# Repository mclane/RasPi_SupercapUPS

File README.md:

# RasPi_SupercapUPS
Expansion board with UPS using supercaps and a special wadchdog/undervoltage detection

## Motivation
I am running a Raspberry Pi in a holiday home. This device also  controls the heating of the water pipes in winter, so it is "mission critical". It also allows to remotly switch on the room heating via sms text messages. Regular status messages are also provided via sms. These functions have been implemented using the smart-home suite iobroker (https://www.iobroker.net/).
Since the electricity grid is sometimes unreliable, a power buffer is needed to have enough time to shut down everything in case of a power loss. Since I do not want to use the usual lithium ion battery based UPS available on the market; I was looking for an alternative and found this: https://www.hackerspace-ffm.de/wiki/index.php?title=Raspi_EDLC_UPS.
The supercaps provide enough energy to supply the raspi for 20 - 30 s which is enough for a safe shutdown. The status of the power supply is provided to one of the GPIO pins of the raspi. The status of this pin is monitored by an iobroker function and a system shutdown command is initiated if a power loss is detected.

## Requirements
- provide enough energy for a safe shutdown of the raspberry pi
- provide a power loss signal
- provide an undervoltage / power good signal to trigger a reboot after power loss
- provide a watchdog to avoid a system hangup (e.g. in case of a short power loss when undervoltage conditions are not yet met)
## Optional requirements
- provide a relay output to control room heating
- measure the actual raspberry pi supply voltage provided by the supercaps
- provide a socket for an I2C real-time clock module
## Implementation
The device is implemented as an accessory pcb to be mounted on top of the raspberry. It consists of the energy storage block and a watchdog block. Furthermore, I have added a relay to be able to switch on the electrical room heating from remote via a sms text message.
### Energy Buffer
The energy buffer consists of 2x 50F supercaps in series with a charge balancer circuit and a charge current limiting resistor. The capacitor bank is decoupled with Schottky diodes from the external power supply. Therefore, the power supply needs to provide a slightly higher voltage, e.g. 5.5V in order to obtain a 5 V supply voltage at the raspi.
### Watchdog and undervoltage detection
The boot process of the RasPi from initial startup until all ioBroker modules and functions are up and running takes about 1:20 min. This means that the watchdog timeout needs to be longer than this in order to allow a correct boot process of the system since one ioBroker function then periodically resets the watchdog timer via the GPIO22 pin. Since I could not find a watchdog IC combining a (programmable) watchdog dead time of 2 min (to be on the safe side) with a precise enough undervoltage detector, I have implemented this function using an Atmel ATTINY85 microcontroller. If an undervoltage event occurs or the watchdog timer expires, a Reset signal is applied to the RUN pin of the raspi. Even though this controller has enough memory so that the functionality could be implemented using the Arduino programming environment, I decided that I wanted to learn something new - so the functionality has been implemented in Assembler.
Since the Raspi provides an SPI interface, the ATTINY can be directly programmed using avrdude.
### Relay stage
This is straightforward: a Darlington (overdimensioned, but this was the one I had in my stock) connected to GPIO27 controls the relay. 
### Miscellaneous
Connector blocks are provided to hook up an external indicator LED for the relay and a voltmeter module to measure the raspberry pi supply voltage. Furthermore, a real-time clock module can be connected via a 4 pin header in vertical position.
## Hardware
KiCad schematics and pcb layout is provided in the hardware directory; Gerber and drill files can be found in the CAM subdirectory. Attention! the extension board has been designed for the Raspberry Pi version 3B; other versions have different positions of the RUN pin; so change the layout accordingly.
## Software
I used VSCode and PlatformIO as development environment:
- create a new PlatformIO project as generic attiny85 project
- modify the platform.ini file as indicated in the platformio.ini file provided here,
- copy the src/main.S file into the src directory of your project
- build 
- and upload using programmer.

For the prototype development, flashing of the Attiny was done outside of the circuit. An AVR Dragon debugger was used for initial flash programming. The appropriate platformio.ini file is provided here. 
The steps to program the Attiny directly from the raspi can be found e.g. in https://www.instructables.com/id/Programming-the-ATtiny85-from-Raspberry-Pi/. Upload the .pio/build/attiny85/firmware.hex file to your Raspberry Pi from the development PC and flash this file using avrdude as described.
The iobroker functionality is not provided here. Resetting of the watchdog timer can also be accomplished via a cron job directly.

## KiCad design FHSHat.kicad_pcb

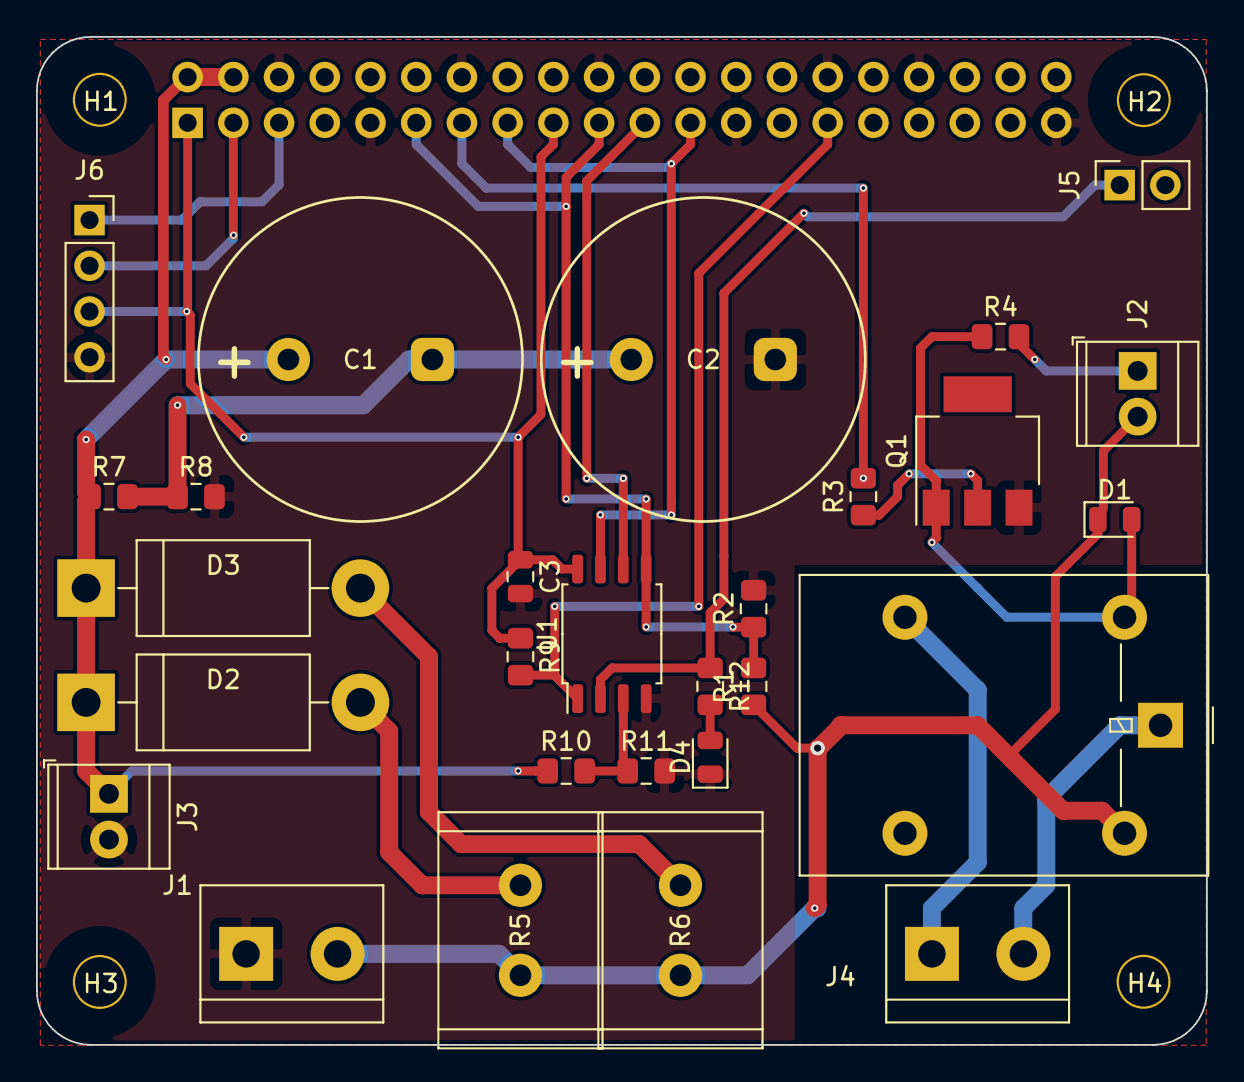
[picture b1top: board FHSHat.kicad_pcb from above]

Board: 2 copper layers, 65.0 x 56.0 mm, 33 parts (1 on the bottom side), 22 nets.

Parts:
C1, C2: 50F; SuperCap
C3: 100n; C_0805_2012Metric
D1: 1N4148; D_0805_2012Metric
D2, D3: 1N5822; D_DO-201AD_P15.24mm_Horizontal
D4: LED gn; LED_0805_2012Metric
H1, H2, H3, H4: 3mm_Mounting_Hole; NPTH_3mm_ID
J1: DC Pwr; TerminalBlock_bornier-2_P5.08mm
J2: LED Rel.; TerminalBlock_TE_282834-2_1x02_P2.54mm_Horizontal
J3: Meter; TerminalBlock_TE_282834-2_1x02_P2.54mm_Horizontal
J4: Ladeschütz; TerminalBlock_bornier-2_P5.08mm
J5: RASPI_RST; PinSocket_1x02_P2.54mm_Vertical
J6: RTC; PinSocket_1x04_P2.54mm_Vertical
J7: 40HAT; PinSocket_2x20_P2.54mm_Vertical
K1: G5LE-1; Relay_SPDT_Omron-G5LE-1
Q1: BSP52; SOT-223
R1, R2, R12: 1k; R_0805_2012Metric_Pad1.15x1.40mm_HandSolder
R3: 10k; R_0805_2012Metric_Pad1.15x1.40mm_HandSolder
R4: 220; R_0805_2012Metric_Pad1.15x1.40mm_HandSolder
R5, R6: 1R5 5W; R_Radial_Power_L13.0mm_W9.0mm_P5.00mm
R7, R8: 100; R_0805_2012Metric_Pad1.15x1.40mm_HandSolder
R9: 47k; R_0805_2012Metric_Pad1.15x1.40mm_HandSolder
R10: 27k; R_0805_2012Metric_Pad1.15x1.40mm_HandSolder
R11: 22k; R_0805_2012Metric_Pad1.15x1.40mm_HandSolder
U1: ATtiny85-20SU; SOIC-8_5.275x5.275mm_P1.27mm

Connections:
+3V3: C3.1, J6.3, J7.1, J7.17, R9.1, U1.8
+5V: C1.1, D2.1, D3.1, J3.1, J7.2, J7.4, R7.1, R10.1
GND: C2.2, C3.2, D4.1, J1.1, J3.2, J6.4, J7.6, J7.9, J7.14, J7.20, J7.25, J7.30, J7.34, J7.39, Q1.3, R2.2, R8.2, R11.2, U1.4
HLS: J7.13, R3.2
MISO: J7.21, U1.6
MOSI: J7.11, J7.19, R1.2, R2.1, U1.5
unnamed: C1.2, C2.1, R7.2, R8.1
unnamed: D1.2, K1.2, Q1.1, R4.1
unnamed: D2.2, R5.1
unnamed: D3.2, R6.1
unnamed: D4.2, R12.2
unnamed: J2.1, R4.2
unnamed: J4.1, K1.3
unnamed: J4.2, K1.1
unnamed: J5.1, R12.1, U1.2
unnamed: Q1.2, R3.1
unnamed: R10.2, R11.1, U1.3
RST: J7.29, R9.2, U1.1
SCL: J6.1, J7.5
SDA: J6.2, J7.3
SPISCL: J7.15, J7.23, U1.7
VCC: D1.1, J1.2, J2.2, K1.5, R1.1, R5.2, R6.2

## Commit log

2019-11-05 Create junk
